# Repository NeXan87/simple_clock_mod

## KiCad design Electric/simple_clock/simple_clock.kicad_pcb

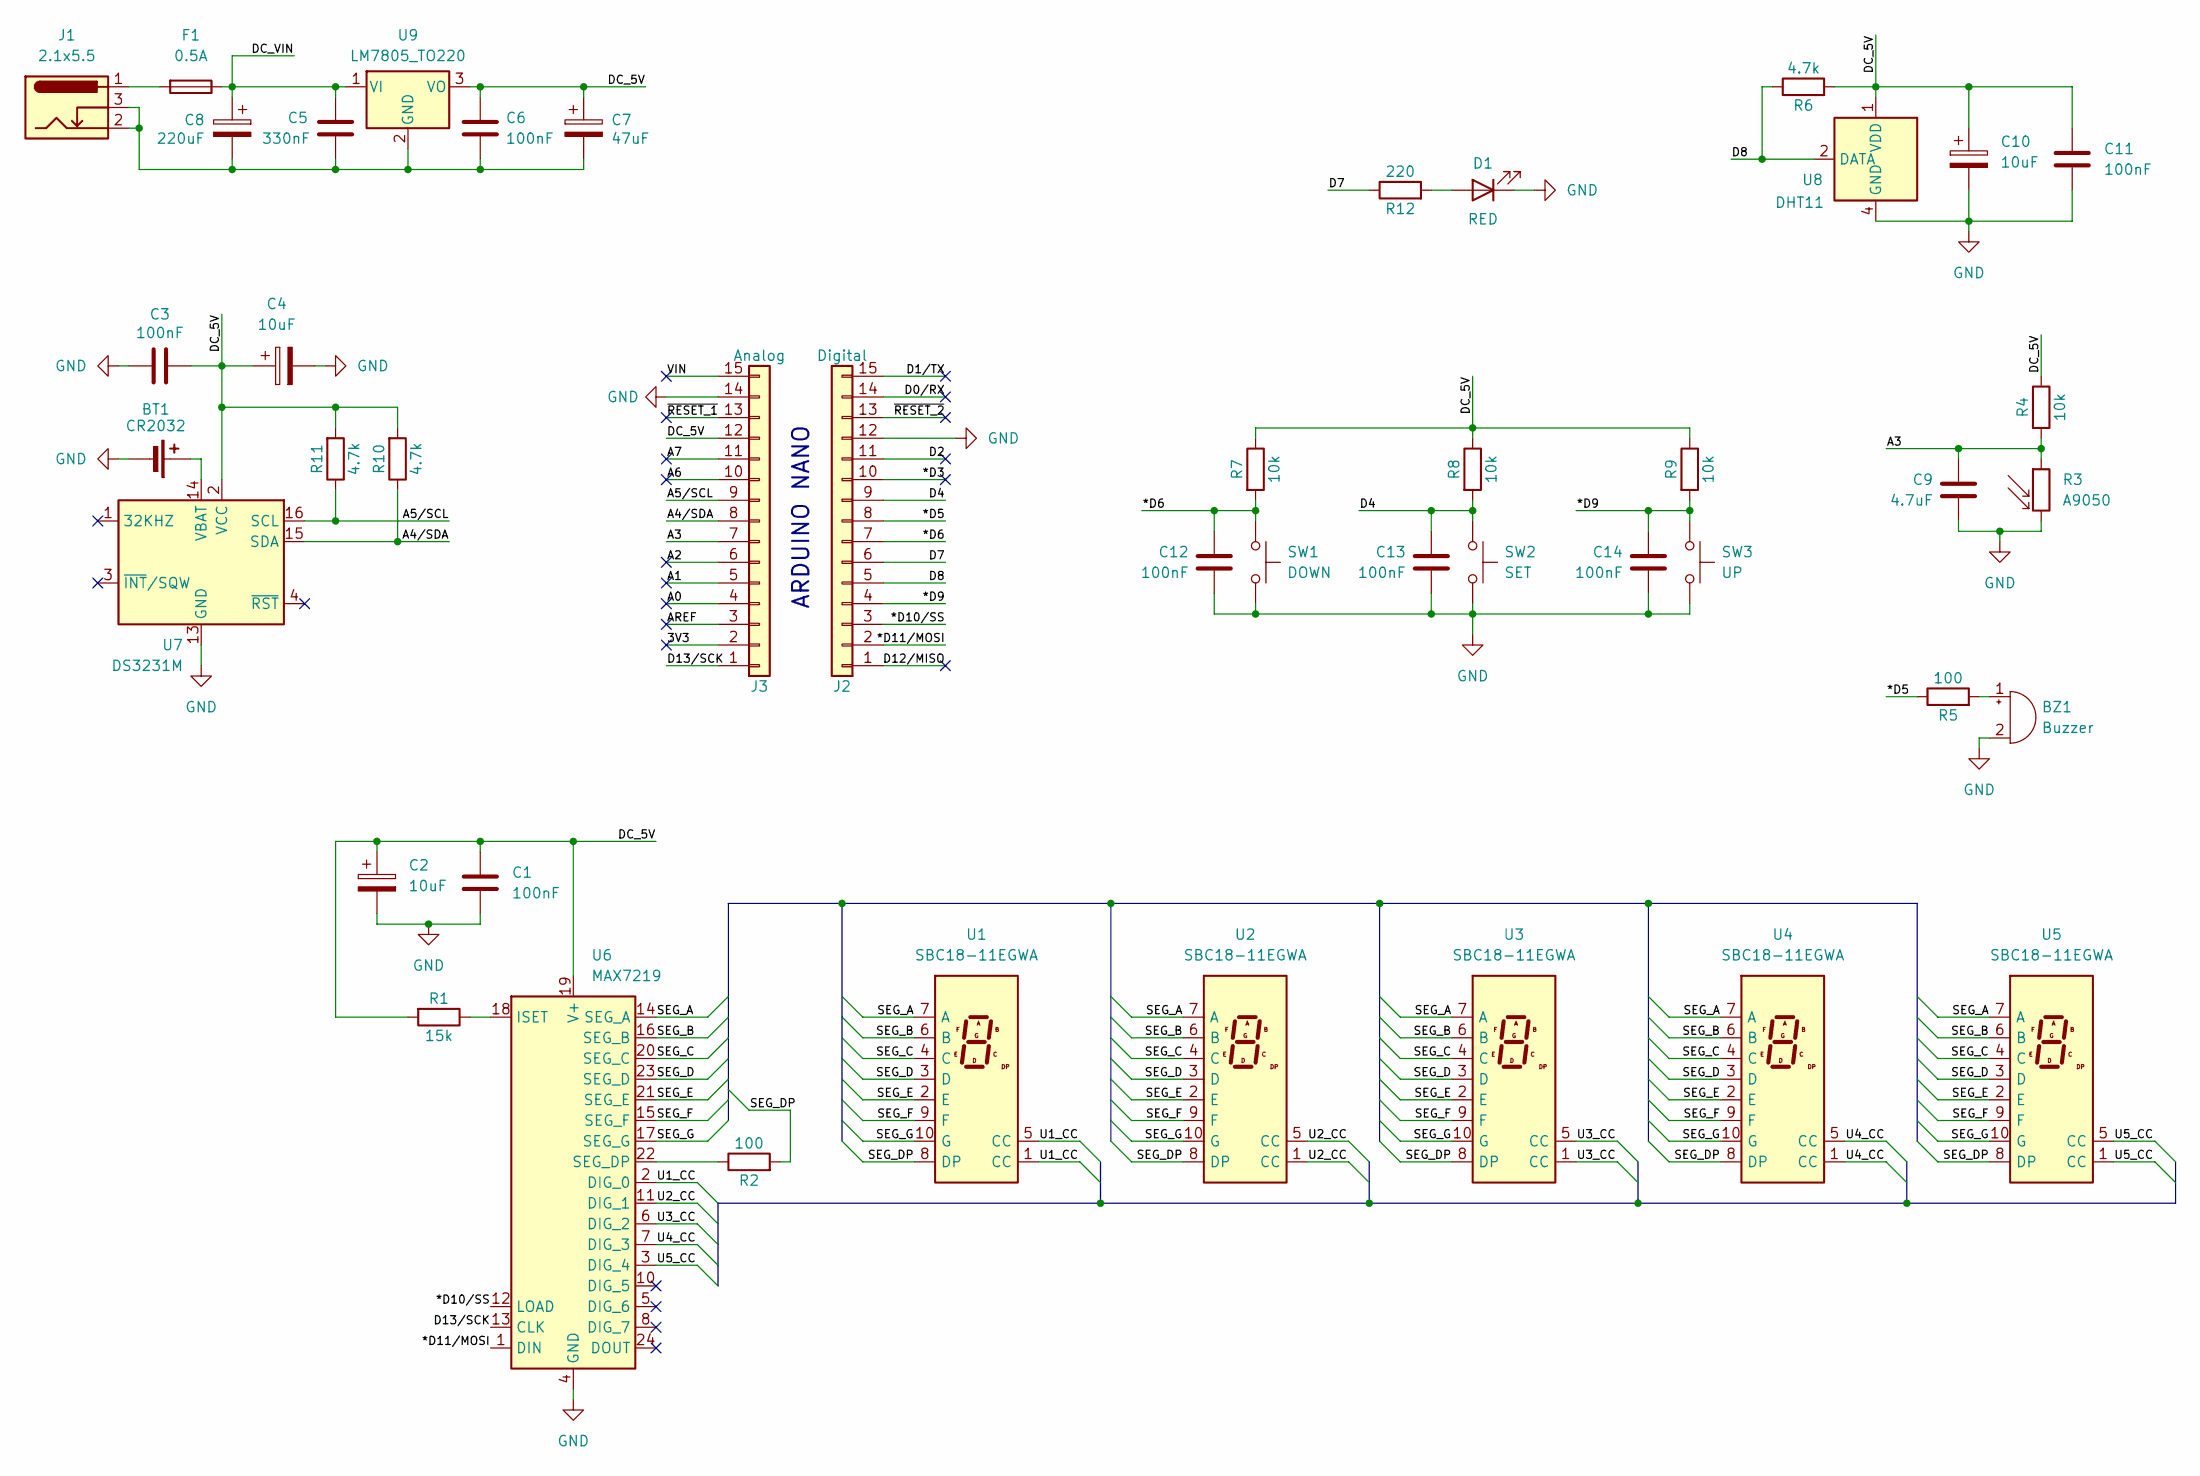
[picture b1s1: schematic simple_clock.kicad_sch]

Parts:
BT1: CR2032; Battery_Panasonic_CR2032-HFN_Horizontal_CircularHoles
BZ1: Buzzer; Buzzer_12x9.5RM7.6
C1, C3, C6, C11, C12, C13, C14: 100nF; C_Axial_L5.1mm_D3.1mm_P10.00mm_Horizontal
C2, C4, C10: 10uF; CP_Radial_D6.3mm_P2.50mm
C5: 330nF; C_Axial_L5.1mm_D3.1mm_P10.00mm_Horizontal
C7: 47uF; CP_Radial_D6.3mm_P2.50mm
C8: 220uF; CP_Radial_D6.3mm_P2.50mm
C9: 4.7uF; C_Axial_L5.1mm_D3.1mm_P10.00mm_Horizontal
D1: RED; LED_D3.0mm
F1: 0.5A; Fuseholder_Clip-5x20mm_Littelfuse_111_Inline_P20.00x5.00mm_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
J1: 2.1x5.5; BarrelJack_Kycon_KLDX-0202-xC_Horizontal
J2: Digital; PinHeader_1x15_P2.54mm_Vertical
J3: Analog; PinHeader_1x15_P2.54mm_Vertical
R1: 15k; R_Axial_DIN0309_L9.0mm_D3.2mm_P12.70mm_Horizontal
R2, R5: 100; R_Axial_DIN0309_L9.0mm_D3.2mm_P12.70mm_Horizontal
R3: A9050; R_LDR_5.0x4.1mm_P3mm_Vertical
R4, R7, R8, R9: 10k; R_Axial_DIN0309_L9.0mm_D3.2mm_P12.70mm_Horizontal
R6, R10, R11: 4.7k; R_Axial_DIN0309_L9.0mm_D3.2mm_P12.70mm_Horizontal
R12: 220; R_Axial_DIN0309_L9.0mm_D3.2mm_P12.70mm_Horizontal
SW1: DOWN; SW_PUSH-12mm_Wuerth-430476085716
SW2: SET; SW_PUSH-12mm_Wuerth-430476085716
SW3: UP; SW_PUSH-12mm_Wuerth-430476085716
U1, U2, U3, U4, U5: SBC18-11EGWA; D1X8K
U6: MAX7219; DIP-24_W7.62mm_LongPads
U7: DS3231M; SOIC-16W_7.5x10.3mm_P1.27mm
U8: DHT11; Aosong_DHT11_5.5x12.0_P2.54mm
U9: LM7805_TO220; TO-220-3_Vertical

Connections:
/3V3: J3.2
/*D3: J2.10
/*D5: J2.8, R5.1
/*D6: C12.1, J2.7, R7.2, SW1.1
/*D9: C14.1, J2.4, R9.2, SW3.1
/*D10/SS: J2.3, U6.12 (LOAD)
/*D11/MOSI: J2.2, U6.1 (DIN)
/A0: J3.4
/A1: J3.5
/A2: J3.6
/A3: C9.1, J3.7, R3.1, R4.2
/A4/SDA: J3.8, R10.1, U7.15 (SDA)
/A5/SCL: J3.9, R11.1, U7.16 (SCL)
/A6: J3.10
/A7: J3.11
/AREF: J3.3
/D0/RX: J2.14
/D1/TX: J2.15
/D2: J2.11
/D4: C13.1, J2.9, R8.2, SW2.1
/D7: J2.6, R12.1
/D8: J2.5, R6.1, U8.2 (DATA)
/D12/MISO: J2.1
/D13/SCK: J3.1, U6.13 (CLK)
/DC_5V: C1.1, C2.1, C3.1, C4.1, C6.1, C7.1, C10.1, C11.1, J3.12, R1.2, R4.1, R6.2, R7.1, R8.1, R9.1, R10.2, R11.2, U6.19 (V+), U7.2 (VCC), U8.1 (VDD), U9.3 (VO)
/DC_VIN: C5.1, C8.1, F1.1, U9.1 (VI)
/SEG_A: U1.7 (A), U2.7 (A), U3.7 (A), U4.7 (A), U5.7 (A), U6.14 (SEG_A)
/SEG_B: U1.6 (B), U2.6 (B), U3.6 (B), U4.6 (B), U5.6 (B), U6.16 (SEG_B)
/SEG_C: U1.4 (C), U2.4 (C), U3.4 (C), U4.4 (C), U5.4 (C), U6.20 (SEG_C)
/SEG_D: U1.3 (D), U2.3 (D), U3.3 (D), U4.3 (D), U5.3 (D), U6.23 (SEG_D)
/SEG_DP: R2.2, U1.8 (DP), U2.8 (DP), U3.8 (DP), U4.8 (DP), U5.8 (DP)
/SEG_E: U1.2 (E), U2.2 (E), U3.2 (E), U4.2 (E), U5.2 (E), U6.21 (SEG_E)
/SEG_F: U1.9 (F), U2.9 (F), U3.9 (F), U4.9 (F), U5.9 (F), U6.15 (SEG_F)
/SEG_G: U1.10 (G), U2.10 (G), U3.10 (G), U4.10 (G), U5.10 (G), U6.17 (SEG_G)
/U1_CC: U1.1 (CC), U1.5 (CC), U6.2 (DIG_0)
/U2_CC: U2.1 (CC), U2.5 (CC), U6.11 (DIG_1)
/U3_CC: U3.1 (CC), U3.5 (CC), U6.6 (DIG_2)
/U4_CC: U4.1 (CC), U4.5 (CC), U6.7 (DIG_3)
/U5_CC: U5.1 (CC), U5.5 (CC), U6.3 (DIG_4)
/VIN: J3.15
/~RESET_1: J3.13
/~RESET_2: J2.13
GND: BT1.2 (-), BZ1.2 (-), C1.2, C2.2, C3.2, C4.2, C9.2, C10.2, C11.2, C12.2, C13.2, C14.2, D1.1 (K), J2.12, J3.14, R3.2, SW1.2, SW2.2, SW3.2, U6.4 (GND), U6.9 (GND), U7.5 (GND), U7.6 (GND), U7.7 (GND), U7.8 (GND), U7.9 (GND), U7.10 (GND), U7.11 (GND), U7.12 (GND), U7.13 (GND), U8.4 (GND)
unnamed: BT1.1 (+), U7.14 (VBAT)
unnamed: BZ1.1 (+), R5.2
unnamed: D1.2 (A), R12.2
unnamed: F1.2, J1.1
unnamed: R1.1, U6.18 (ISET)
unnamed: R2.1, U6.22 (SEG_DP)
unnamed: C5.2, C6.2, C7.2, C8.2, J1.2, J1.3, U9.2 (GND)

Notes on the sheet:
ARDUINO NANO

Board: 2 copper layers, 45 parts (0 on the bottom side), 35 nets, no tracks yet.
